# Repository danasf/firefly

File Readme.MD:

Programmable Touch Firefly Jar 
================================

Programmable touch firefly lamp. For use with ATtiny85 (or Arduino!) and [Neopixel](https://www.adafruit.com/categories/37) (WS2811/12/12B) RGB LEDs. 

Full build details over at [Instructables](http://www.instructables.com/id/Programmable-LED-Firefly-Jar/).

You can grab PCBs via [OSHPark](http://oshpark.com/shared_projects/p76iCXLt).

Instructions
------------

* Download Adafruit's [NeoPixel](https://github.com/adafruit/Adafruit_NeoPixel) library and the [Capacitive Sense](http://playground.arduino.cc//Main/CapacitiveSensor) library
* Get the [ATtiny cores](https://code.google.com/p/arduino-tiny/) for Arduino & a [programmer](https://www.adafruit.com/products/46)
* Attach your LED data line to Digital Pin 4
* Attach lid/touch sensor to Digital Pins 0 & 1
* Enjoy your technicolor LED light show

More Info
------------

Need help getting started with ATtiny and lights? I wrote an [Instructable](http://www.instructables.com/id/Use-a-1-ATTiny-to-drive-addressable-RGB-LEDs/) on that too.

If you're seeing 'R_AVR_13_PCREL' errors when you try to compile, try this [thread](http://forum.arduino.cc/index.php?topic=116674.0) for solutions. This is a known problem with Arduino IDE, ATtiny and sketches > 4k.

Acknowledgements
------------

Much thanks to [Adafruit](http://adafruit.com) for their NeoPixel Library, wonderful tutorials and all the work they do for open source, hardware hacking communities. Support them!

[Funkboxing](http://funkboxing.com/wordpress/?p=2154) for inspiring and cool LED effects and helper functions.

[Instructables](http://instructables.com) for featuring my project and a lovely community.

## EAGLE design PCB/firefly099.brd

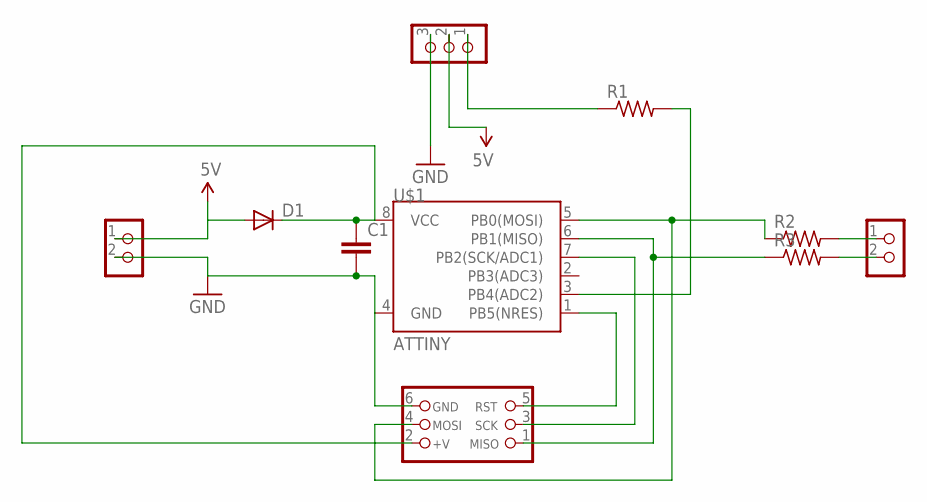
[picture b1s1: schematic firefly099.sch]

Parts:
-,+: CON_TERMINAL_BLOCK_02-5MM; TERMINAL_BLOCK_2P_5
C1: CAPPTH; CAP-PTH-SMALL
D1: 1N4004; DO41-10
IO: CON_TERMINAL_BLOCK_02-5MM; TERMINAL_BLOCK_2P_5
J3: CON_HEADER_PRG_AVR_ICSP-PTH; HEADER_PRG_2X03
LED: CON_TERMINAL_BLOCK_03-5MM; TERMINAL_BLOCK_3P_5
R1, R2, R3: R-US_0207/2V; 0207/2V
U$1: ATTINY; DIP08

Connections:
5V: -,+.1, D1.A, LED.2
GND: -,+.2, C1.2, J3.6 (GND), LED.3, U$1.4 (GND)
unnamed: C1.1, D1.C, J3.2 (+V), U$1.8 (VCC)
unnamed: J3.5 (RST), U$1.1 (PB5(NRES))
unnamed: J3.3 (SCK), U$1.7 (PB2(SCK/ADC1))
unnamed: J3.1 (MISO), R3.1, U$1.6 (PB1(MISO))
unnamed: J3.4 (MOSI), R2.1, U$1.5 (PB0(MOSI))
unnamed: R1.2, U$1.3 (PB4(ADC2))
unnamed: IO.1, R2.2
unnamed: LED.1, R1.1
unnamed: IO.2, R3.2

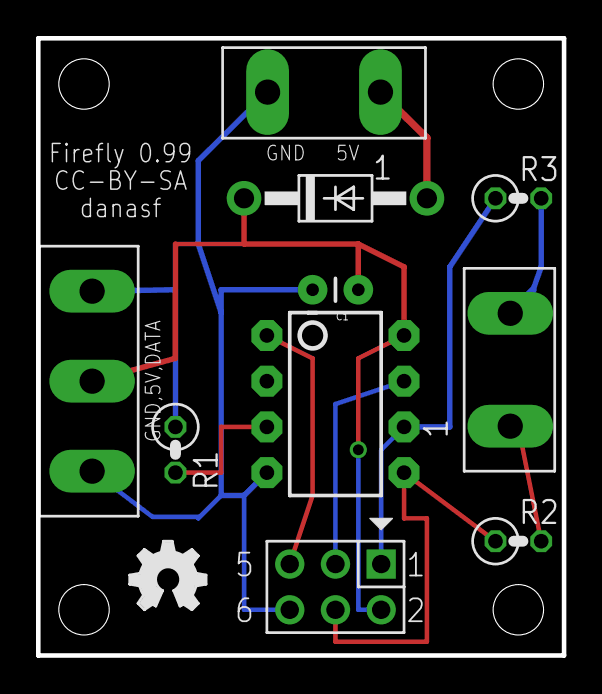
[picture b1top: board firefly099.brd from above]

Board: 2 copper layers, 29.2 x 34.3 mm, 11 parts (0 on the bottom side), 11 nets.

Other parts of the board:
U$4: OSHW_FILLX150_NOTEXT

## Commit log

2014-06-03 commit time :)
2014-06-03 Rename Readme.MD to readme.md
2014-06-03 Added troubleshooting
2014-06-06 more info
2014-06-09 minor language ch

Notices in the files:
PCB/firefly099.brd:
CC-BY-SA
parts and their libraries:
SparkFun: Licensing: CC v3.0 Share-Alike You are welcome to use this library for commercial purposes.
